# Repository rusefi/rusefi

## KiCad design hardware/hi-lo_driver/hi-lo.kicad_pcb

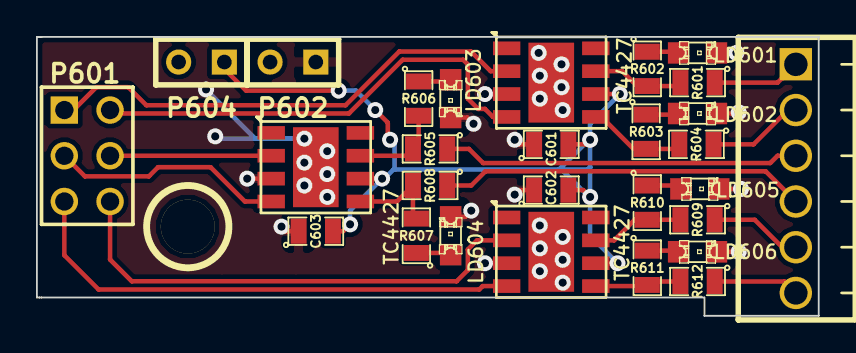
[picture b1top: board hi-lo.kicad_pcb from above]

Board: 2 copper layers, 43.4 x 15.5 mm, 30 parts (1 on the bottom side), 26 nets.

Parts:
C601, C602, C603: 0.1uF; SM0805
G601: LOGO; LOGO_F
LD601, LD602, LD603, LD604, LD605, LD606: LED; LED-0805
M601: CONN_1; 1pin
P601: CONN_3X2; pin_array_3x2
P602, P604: CONN_2; SIL-2
P603: CONN_6; OSTVN06A150
R601, R604, R605, R608, R609, R612: 100; SM0805
R602, R603, R606, R607, R610, R611: 2700; SM0805
U601, U602, U603: TC4427; SOIC8-DFN

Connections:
/HL1: P603.1, R601.1
/HL2: P603.2, R604.1
/HL3: P603.3, R605.1
/HL4: P603.4, R608.1
/HL5: P603.5, R609.1
/HL6: P603.6, R612.1
/H_IN1: P601.2, U601.4
/H_IN2: P601.4, U602.2
/H_IN3: P601.1, U601.2
/H_IN4: P601.3, U602.4
/H_IN5: P601.5, U603.4
/H_IN6: P601.6, U603.2
/VP: C601.2, C602.2, C603.2, P604.1, U601.6, U602.6, U603.6
GND: C601.1, C602.1, C603.1, LD601.2, LD602.2, LD603.2, LD604.2, LD605.2, LD606.2, P602.1, U601.3, U601.9, U602.3, U602.9, U603.3, U603.9
unnamed: LD604.1, R607.1
unnamed: LD602.1, R603.1
unnamed: LD605.1, R610.1
unnamed: LD603.1, R606.1
unnamed: LD601.1, R602.1
unnamed: R609.2, R610.2, U603.7
unnamed: R603.2, R604.2, U601.5
unnamed: R601.2, R602.2, U601.7
unnamed: R607.2, R608.2, U602.5
unnamed: R605.2, R606.2, U602.7
unnamed: LD606.1, R611.1
unnamed: R611.2, R612.2, U603.5

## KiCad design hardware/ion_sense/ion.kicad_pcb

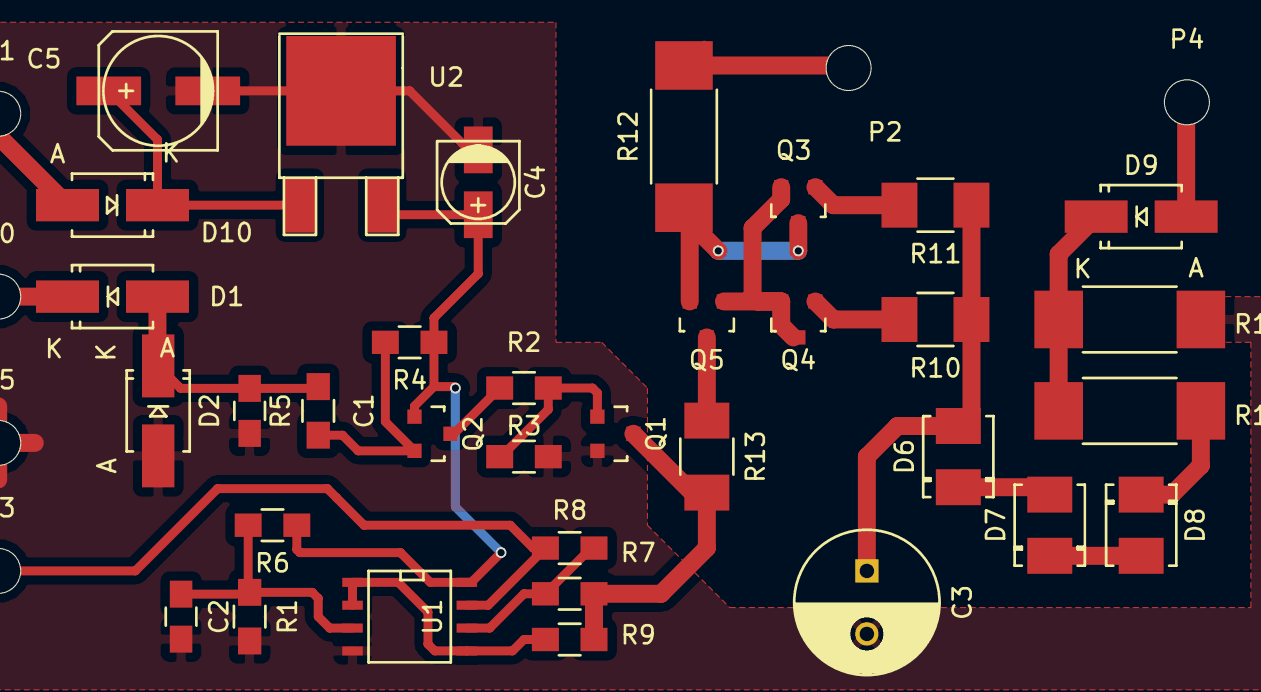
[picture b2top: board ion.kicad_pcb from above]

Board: 2 copper layers, 40 parts (0 on the bottom side), 25 nets.

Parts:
C1: 0.1uF; C_0805_HandSoldering
C2: 1uF; C_0805_HandSoldering
C3: 2.2uF 350V; C_Radial_D8_L11.5_P3.5
C4: 4.7uF 16V; c_elec_4x4.5
C5: 47uF 25V; c_elec_6.3x4.5
D1, D2, D9, D10: US1M; SMA_Handsoldering
D6, D7, D8: 1N4740A; DO-214BA
P0, P1, P2, P3, P4, P5: CONN_01X01; MountingHole_2-5mm
Q1: MMBT3904; SOT-23
Q2, Q3, Q4, Q5: MPSA92; SOT-23
R1, R6, R7, R8: 51k; R_0805_HandSoldering
R2: 2k; R_0805_HandSoldering
R3: 3.9k; R_0805_HandSoldering
R4: 10k; R_0805_HandSoldering
R5: 1k; R_0805_HandSoldering
R9: 4.7k; R_0805_HandSoldering
R10, R11: 560; R_1210_HandSoldering
R12: 180k; R_2512_HandSoldering
R13: 68k; R_1210_HandSoldering
R14: 33k; R_2512_HandSoldering
R15: 1M; R_2512_HandSoldering
U1: LM2904; SOIC-8-N
U2: MC78M05CDT; TO-252-2Lead

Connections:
Earth: C1.2, C2.2, C3.2, C4.2, C5.2, D2.2, P5.1, Q1.2, R1.2, R2.2, R15.1, U1.4, U2.2
unnamed: C1.1, D1.2, D2.1, R5.2
unnamed: C2.1, R1.1, R6.2, U1.3
unnamed: C3.1, D6.2, R10.1, R11.1
unnamed: C4.1, Q2.1, R4.1, R6.1, U1.8, U2.3
unnamed: C5.1, D10.1, U2.1
unnamed: D1.1, P0.1
unnamed: D6.1, D7.2
unnamed: D7.1, D8.2
unnamed: D8.1, R14.2
unnamed: D9.1, R14.1, R15.2
unnamed: D9.2, P4.1
unnamed: D10.2, P1.1
unnamed: P3.1, R8.1, U1.7
unnamed: Q1.1, R2.1, R3.1
unnamed: Q1.3, R7.1, R9.1, R13.2
unnamed: Q2.2, R4.2, R5.1
unnamed: Q2.3, R3.2
unnamed: Q3.1, R11.2
unnamed: Q3.2, Q4.2, Q4.3, Q5.1
unnamed: Q3.3, Q5.2, R12.1
unnamed: Q4.1, R10.2
unnamed: Q5.3, R13.1
unnamed: R7.2, R8.2, U1.6
unnamed: R9.2, U1.1, U1.2, U1.5

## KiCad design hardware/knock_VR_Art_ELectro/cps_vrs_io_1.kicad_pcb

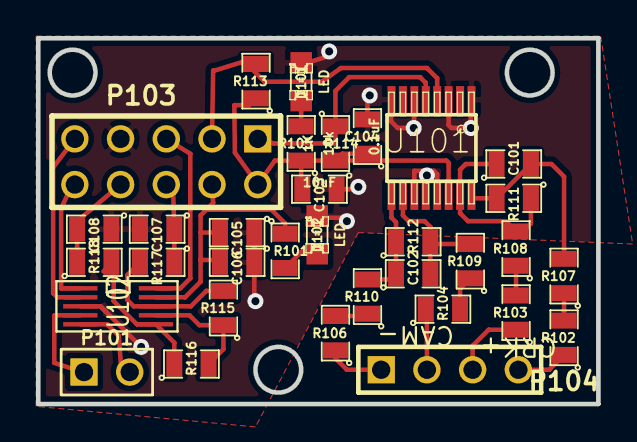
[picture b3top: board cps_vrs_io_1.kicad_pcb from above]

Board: 2 copper layers, 31.1 x 20.3 mm, 34 parts (1 on the bottom side), 29 nets.

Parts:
C101, C102, C108: 1000pF; SM0805
C103: 10uF; SM0805
C104, C106, C107: 0.1uF; SM0805
C105: 1uF; SM0805
D101, D102: LED; LED-0805_A
G101: LOGO; LOGO_F
P101: CONN_2; PIN_ARRAY_2_A
P103: CONN_5X2; PIN_ARRAY_5x2
P104: CONN_4; PIN_ARRAY_4x1
R101, R105: 1K; SM0805
R102, R103, R104, R106, R107, R108, R109, R110, R111, R112: 5k; SM0805
R113, R114: 10k; SM0805
R115, R116: 10K; SM0805
R117, R118: 20K; SM0805
U101: MAX9926/9927; maxim-10-QSOP16
U102: MAX9939; uMAX-uSOP_10

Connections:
/5V: C103.2, C104.1, P103.2, R105.1, R113.1, R114.2, U101.14
/5v stab: C105.2, C106.2, P103.4, R101.1, U102.9
/CAM: P103.1, R114.1, U101.5
/CAM+: P104.1, R106.1
/CAM-: P104.2, R104.1
/CRANK: P103.3, R113.2, U101.4
/CRK2+: P104.4, R102.1
/CRK2-: P104.3, R103.1
/CS-KN1: P103.5, U102.10
/MISO: P103.9, U102.2
/SCK: P103.10, U102.1
/knock1+: C107.1, P103.6, R117.1
/knock1-: C108.2, P103.8, R118.1
/knock_1+p: P101.2, U102.5
/knock_1-p: P101.1, U102.4
GND: C103.1, C104.2, C105.1, C106.1, C107.2, C108.1, D101.2, D102.2, P103.7, U101.1, U101.3, U101.6, U101.8, U101.11, U101.12, U101.13, U102.3
unnamed: R115.1, R116.2, U102.7
unnamed: R115.2, R117.2, U102.8
unnamed: R116.1, R118.2, U102.6
unnamed: D102.1, R101.2
unnamed: D101.1, R105.2
unnamed: R102.2, R107.1
unnamed: R104.2, R109.1
unnamed: R106.2, R110.1
unnamed: R103.2, R108.1
unnamed: C101.1, R108.2, R111.1, U101.15
unnamed: C101.2, R107.2, R111.2, U101.16
unnamed: C102.1, R110.2, R112.1, U101.9
unnamed: C102.2, R109.2, R112.2, U101.10

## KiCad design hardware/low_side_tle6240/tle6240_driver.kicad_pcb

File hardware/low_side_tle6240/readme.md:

TLE6240GP module - integrated low side switch

https://youtu.be/H8Tr4kTaYAI

https://rusefi.com/forum/viewtopic.php?f=4&t=398

All 16 channels can be controlled via the serial interface (SPI). In addition to the serial control it is possible to
control channel 1 to 4 and 9 to 12 direct in parallel with a separate input pin.

https://github.com/rusefi/rusefi_documentation/blob/master/oem_docs/Infineon/Infineon-TLE6240GP-DS-v03_03-en.pdf

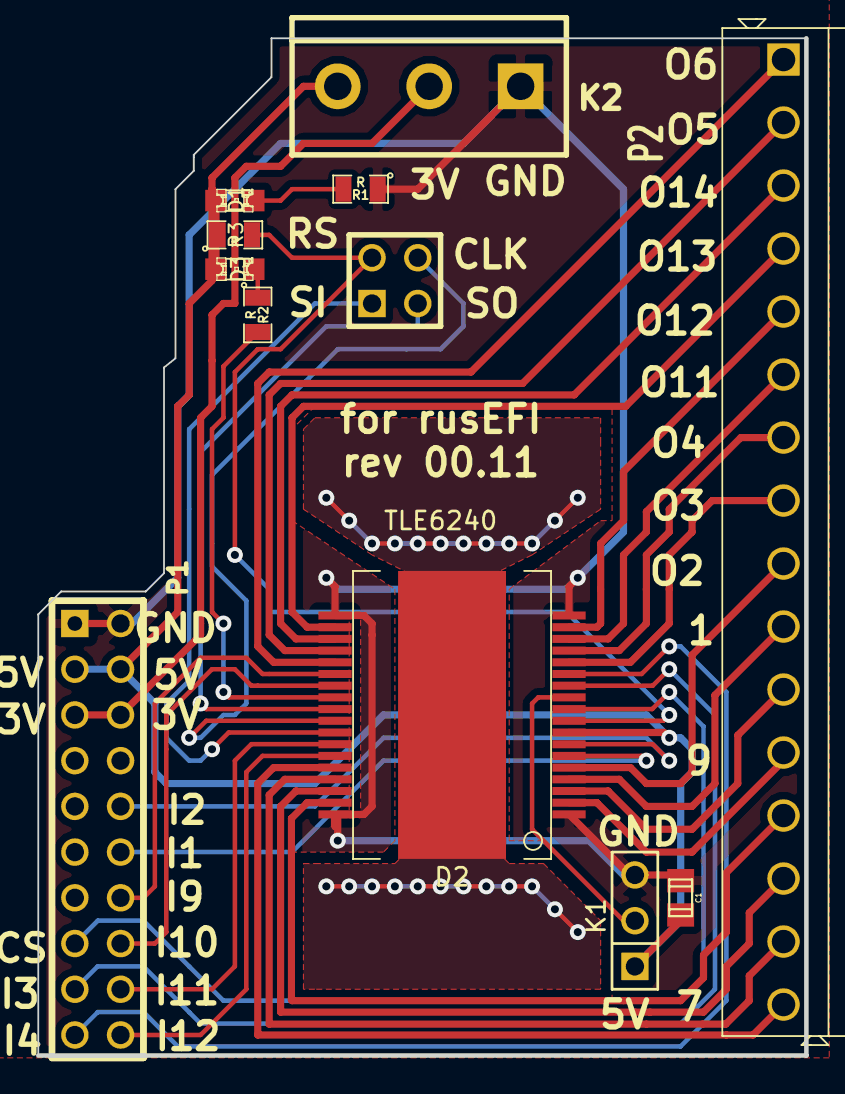
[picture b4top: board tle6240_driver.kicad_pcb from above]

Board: 2 copper layers, 42.7 x 56.5 mm, 12 parts (0 on the bottom side), 36 nets.

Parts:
C1: C; c_0805
D1, D3: LED; LED-0805
D2: TLE6240; PG-DSO-36
K1: JUMPER3; PIN_ARRAY_3X1
K2: CONN_3; bornier3
P1: CONN_10X2; PIN_ARRAY_10X2
P2: CONN_16; SIL-16_3.5MM
P3: CONN_2X2; PIN_ARRAY_2X2
R1, R2, R3: R; SM0805

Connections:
+5V: C1.1, D1.1, D2.8, D3.1, K1.1, K2.3, P1.3, P1.4, R3.1
/+3.3V: K2.2, P1.5, P1.6
/CS: D2.10, P1.15
/Fault: D2.26, R2.2
/IN1: D2.6, P1.12
/IN2: D2.7, P1.10
/IN3: D2.12, P1.17
/IN4: D2.13, P1.19
/IN9: D2.24, P1.14
/IN10: D2.25, P1.16
/IN11: D2.30, P1.18
/IN12: D2.31, P1.20
/OUT1: D2.4, P2.10
/OUT2: D2.5, P2.9
/OUT3: D2.14, P2.8
/OUT4: D2.15, P2.7
/OUT5: D2.22, P2.2
/OUT6: D2.23, P2.1
/OUT7: D2.32, P2.16
/OUT8: D2.33, P2.15
/OUT9: D2.2, P2.12
/OUT10: D2.3, P2.11
/OUT11: D2.16, P2.6
/OUT12: D2.17, P2.5
/OUT13: D2.20, P2.4
/OUT14: D2.21, P2.3
/OUT15: D2.34, P2.14
/OUT16: D2.35, P2.13
/PRG: D2.11, K1.2
/Reset: D2.9, P3.2, R3.2
/SCLK: D2.28, P3.4
/SI: D2.29, P3.1
/SO: D2.27, P3.3
GND: C1.2, D2.1, D2.18, D2.19, D2.36, K1.3, K2.1, P1.1, P1.2, R1.1
unnamed: D3.2, R2.1
unnamed: D1.2, R1.2

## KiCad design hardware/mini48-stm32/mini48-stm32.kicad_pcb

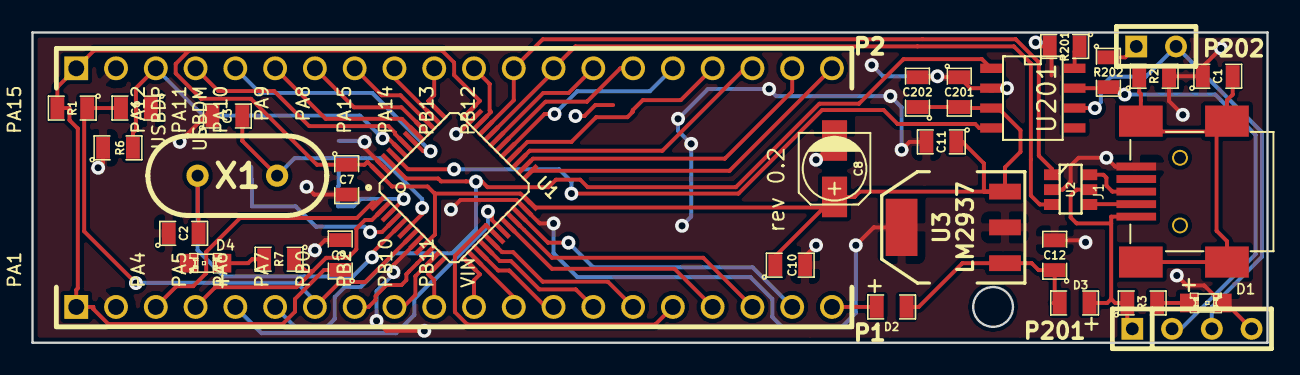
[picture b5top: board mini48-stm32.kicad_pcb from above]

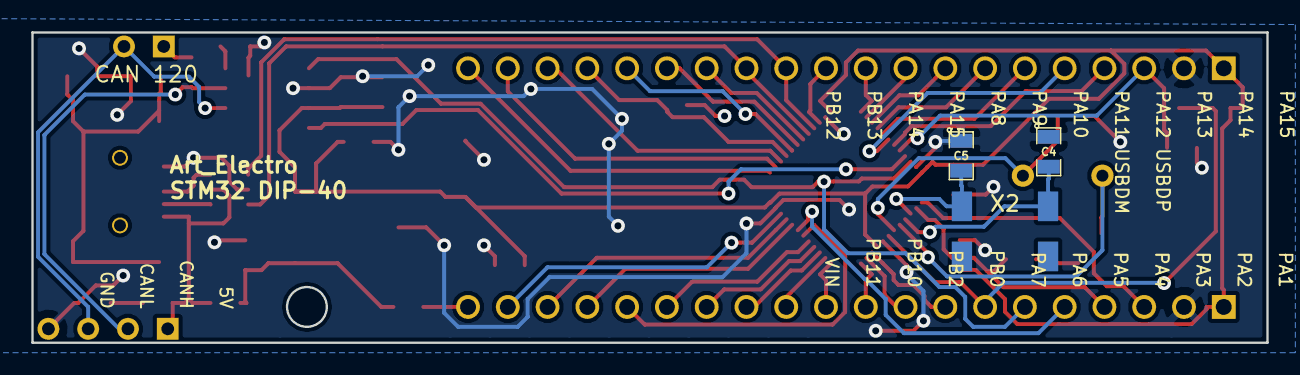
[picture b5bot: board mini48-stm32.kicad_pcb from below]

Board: 2 copper layers, 78.9 x 19.8 mm, 36 parts (3 on the bottom side), 54 nets.

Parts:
C1: 4700pF; SM0805
C2, C3, C4, C5: 18pF; SM0805
C6: 100nF; SM0805
C7, C10, C11: 1uF; SM0805
C8: 47uF; CP_elec_4x5.3
C9, C201: 0.1uF; SM0805
C12: 10uF; SM0805
C202: 4.7uF; SM0805
D1: GREEN; LED-0805_A
D2, D3: DIODESCH; SM0805-diode
D4: BLUE; LED-0805_A
J1: MINI-USB; MINI-USB-5P-3400020P1
P1, P2: CONN_20; PIN_ARRAY_20X1
P201: CONN_4; SIL-4
P202: JUMPER; JUMPER-2
R1, R3, R7: 1k; SM0805
R2: 1M; SM0805
R6, R201: 10k; SM0805
R202: 120; SM0805
U1: STM32F103C8; lqfp48
U2: NUF2101MT1G; SOT-457
U3: LM2937; SOT223
U201: SN65HVD230; SO8E
X1: 8MHz; HC-49V
X2: 32768KHz; MC-306

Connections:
/BOOT0: P2.3, R6.2, U1.44
/CAN BUS/3.3V: C7.1, C8.1, C9.1, C10.1, C11.1, C201.2, C202.1, P1.1, P2.1, R1.2, U1.9, U1.24, U1.36, U1.48, U3.3, U201.3
/CAN BUS/5V: D3.1, J1.1, P201.1, R3.1, U2.5
/CAN BUS/CANH: P201.2, R202.2, U201.7
/CAN BUS/CANL: P201.3, P202.2, U201.6
/CAN BUS/CAN_RX: U1.45, U201.4
/CAN BUS/CAN_TX: P1.6, U1.46, U201.1
/D+: J1.3, U2.6
/D-: J1.2, U2.4
/PA0: P1.8, U1.10
/PA1: P1.9, U1.11
/PA2: P1.10, U1.12
/PA3: P1.11, U1.13
/PA4: P1.12, U1.14
/PA5: P1.13, U1.15
/PA6: P1.14, U1.16
/PA7: P1.15, U1.17
/PA8: P2.16, U1.29
/PA9: P2.15, U1.30
/PA10: P2.14, U1.31
/PA11_USBDM: P2.13, U1.32, U2.3
/PA12_USBDP: P2.12, U1.33, U2.1
/PA13: P2.11, U1.34
/PA14: P2.10, U1.37
/PA15: P2.9, U1.38
/PB0: P1.16, U1.18
/PB1: P1.5, U1.19
/PB2: P1.17, U1.20
/PB3: P2.8, U1.39
/PB4: P2.7, U1.40
/PB5: P2.6, U1.41
/PB6: P2.5, U1.42
/PB7: P2.4, U1.43
/PB10: P1.18, U1.21
/PB11: P1.19, U1.22
/PB12: P2.20, U1.25
/PB13: P2.19, U1.26
/PB14: P2.18, U1.27
/PB15: P2.17, U1.28
/PC13: P1.4, R7.1, U1.2
/PC14_OSC32_IN: C5.2, U1.3, X2.2
/PC15_OSC32_OUT: C4.2, U1.4, X2.1
/PD0: C2.2, U1.5, X1.1
/PD1: C3.2, U1.6, X1.2
/Reset: C6.2, P1.7, R1.1, U1.7
/VBAT: P1.3, U1.1
/VIN: D2.1, P1.20
GND: C1.1, C2.1, C3.1, C4.1, C5.1, C6.1, C7.2, C8.2, C9.2, C10.2, C11.2, C12.2, C201.1, C202.2, D1.2, D4.2, J1.5, P1.2, P2.2, P201.4, R2.2, R6.1, R201.2, U1.8, U1.23, U1.35, U1.47, U2.2, U3.2, U3.4, U201.2
unnamed: C12.1, D2.2, D3.2, U3.1
unnamed: D4.1, R7.2
unnamed: D1.1, R3.2
unnamed: C1.2, J1.6, R2.1
unnamed: P202.1, R202.1
unnamed: R201.1, U201.8

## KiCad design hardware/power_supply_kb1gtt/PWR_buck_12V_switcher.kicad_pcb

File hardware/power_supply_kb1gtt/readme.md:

Older version of the power supply with SMD inductors

For current version with three inductors see [frankenso-PWR-Supply](../frankenso-PWR-Supply)

https://rusefi.com/forum/viewtopic.php?f=4&t=394

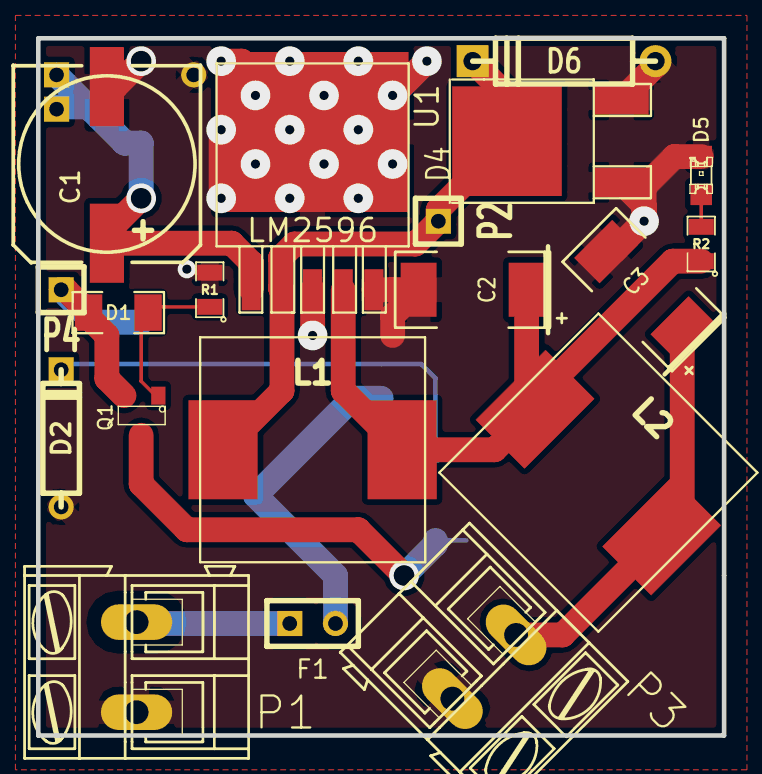
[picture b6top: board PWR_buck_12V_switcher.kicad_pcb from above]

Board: 2 copper layers, 38.1 x 38.7 mm, 24 parts (0 on the bottom side), 12 nets.

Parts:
C1: 330uF 35V; SMDSVP10
C2, C3: 220uF 16V; SM2512
D1: 7.5V; SM1206
D2: 14V; D3
D3: 24V; D3
D4: SCHDPAK; DPAK2
D5: LED-grn; LED-0805
D6: DIODESCH; D4
F1: 5A; SIL-2
L1, L2, L3: 38uH; SM100uH
P1, P3: CONN_2; AK300-2
P2, P4, P5: CONN_1; SIL-1
Q1: 20V; SOT23
Q2: 200V; m-pad-2.1-TO-263AB
R1: 39k; SM0805
R2: 1k; SM0805
R3: 100k; SM0805
U1: LM2596; DPAK5

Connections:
/5V-REG: C3.1, L2.2, P3.1
/FB: C2.1, L1.2, L2.1, R2.1, U1.4
/OUT: D4.2, D6.2, L1.1, P2.1, U1.2
/VBAT: C1.1, D3.2, L3.2, P5.1, U1.1
/Vf: F1.2, Q2.2, R3.1
/Vin: F1.1, P1.2
/Vs1: D2.2, Q2.1, R3.2
/Vs2: Q1.3, Q2.3
GND: C1.2, C2.2, C3.2, D2.1, D3.1, D4.1, D4.3, D5.2, D6.1, P1.1, P3.2, R1.2, U1.3, U1.5
unnamed: D1.1, Q1.1, R1.1
unnamed: D1.2, L3.1, P4.1, Q1.2
unnamed: D5.1, R2.2

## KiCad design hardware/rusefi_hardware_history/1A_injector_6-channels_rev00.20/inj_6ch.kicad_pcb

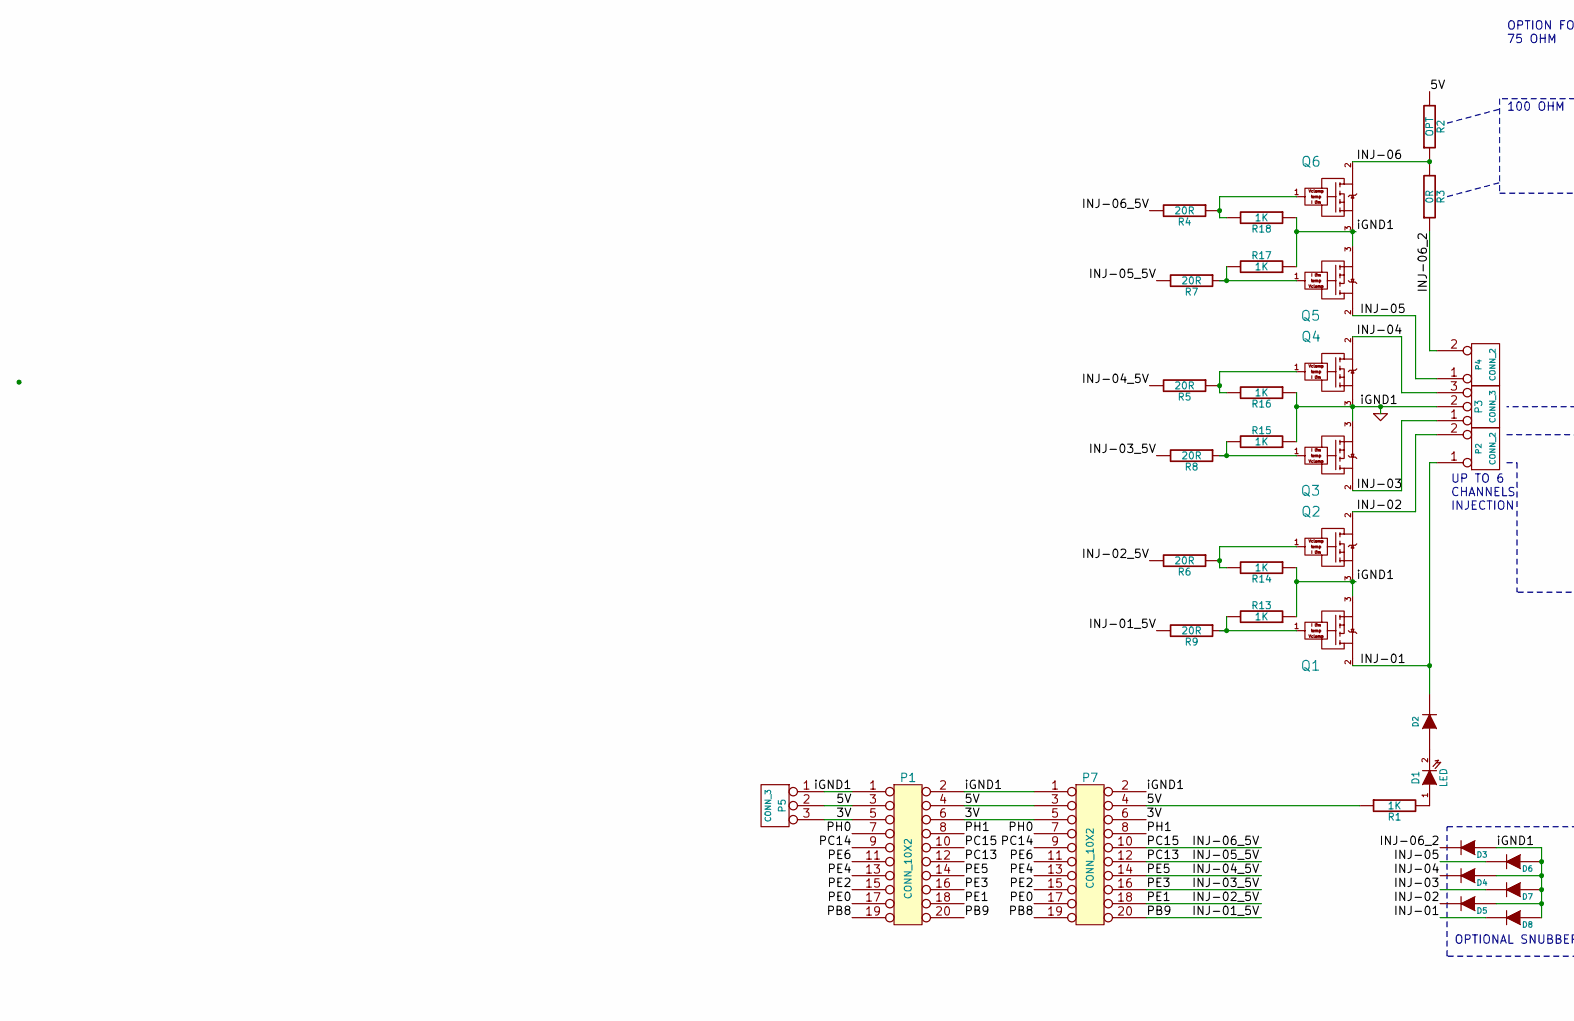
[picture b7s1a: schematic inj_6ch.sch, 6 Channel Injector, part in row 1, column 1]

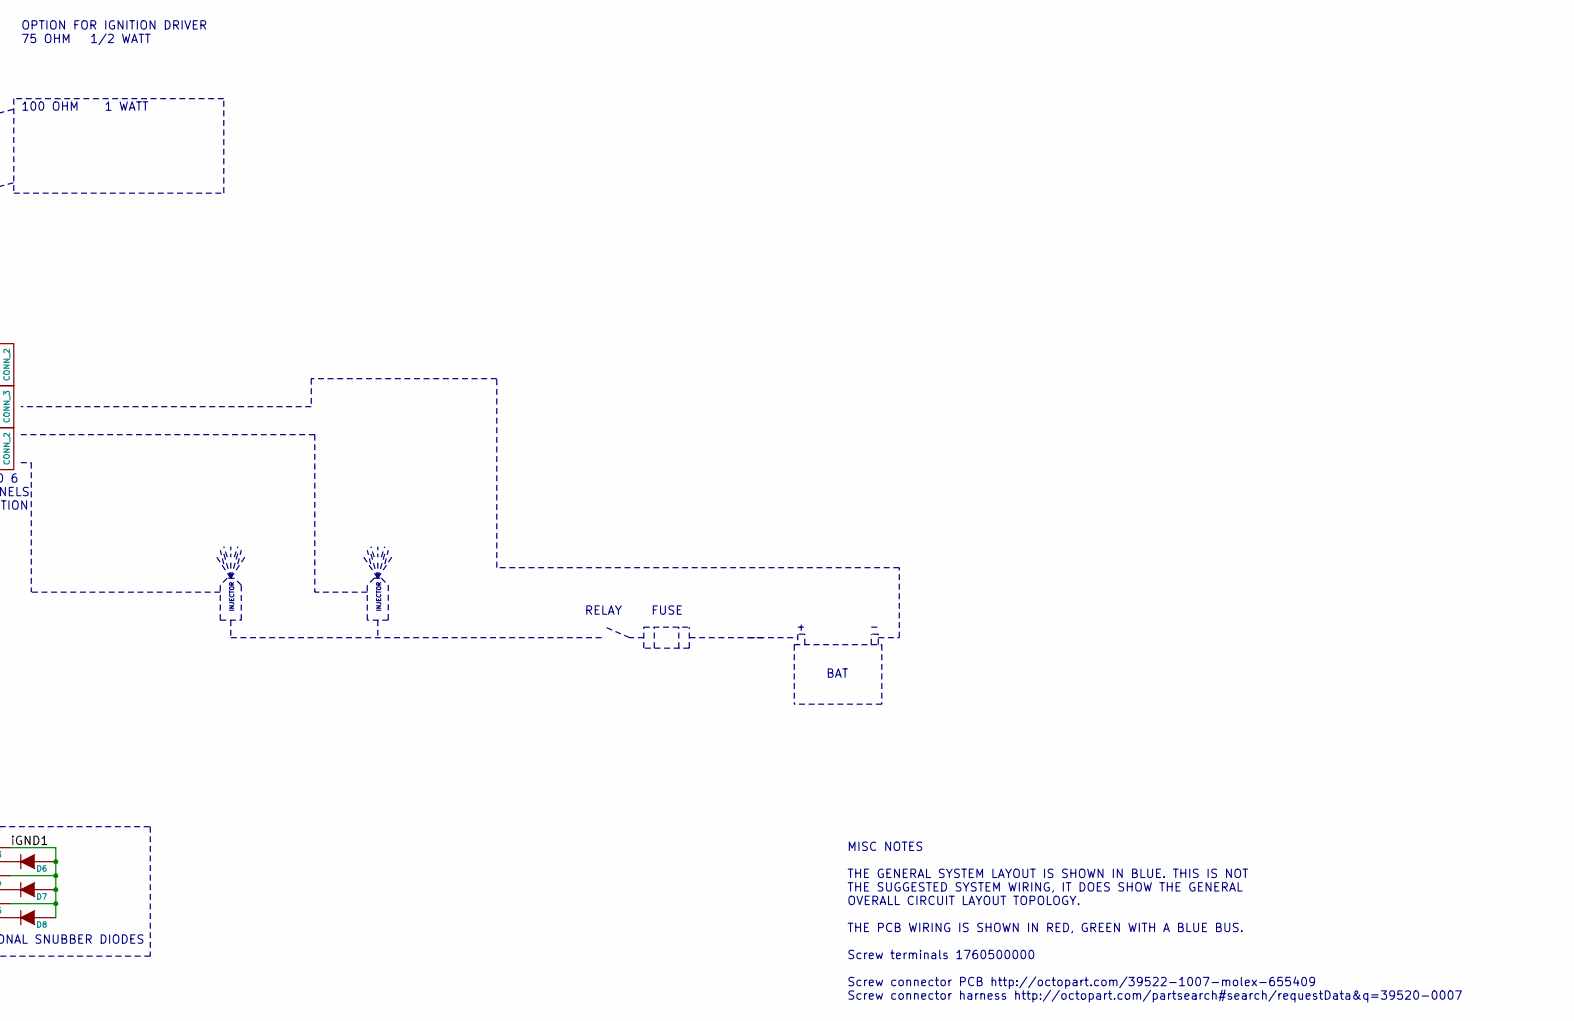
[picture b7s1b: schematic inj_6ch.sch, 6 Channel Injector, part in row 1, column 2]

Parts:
D1: LED; LED-0805
D2: DIODE; SOD-123
D3, D4, D5, D6, D7, D8: DIODE; SIL-2
P1, P7: CONN_10X2; pin_array_10x2
P2, P4: CONN_2; bornier2
P3, P5: CONN_3; bornier3; mfg# 1760500000
Q1, Q2, Q3, Q4, Q5, Q6: OVP_DRIVER; SO8E_ST
R1, R13, R14, R15, R16, R17, R18: 1K; SM0805
R2: OPT; SIL-2
R3: 0R; SIL-2
R4, R5, R6, R7, R8, R9: 20R; SM0805

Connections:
/3V: P1.5, P1.6, P5.3, P7.5, P7.6
/5V: P1.3, P1.4, P5.2 (PM), P7.3, P7.4, R1.1, R2.2
/INJ-01: D2.2 (K), D8.2 (K), P2.1, Q1.2 (C)
/INJ-01_5V: P1.20, P7.20, R9.2
/INJ-02: D5.2 (K), P2.2 (PM), Q2.2 (C)
/INJ-02_5V: P1.18, P7.18, R6.2
/INJ-03: D7.2 (K), P3.1, Q3.2 (C)
/INJ-03_5V: P1.16, P7.16, R8.2
/INJ-04: D4.2 (K), P3.3, Q4.2 (C)
/INJ-04_5V: P1.14, P7.14, R5.2
/INJ-05: D6.2 (K), P4.1, Q5.2 (C)
/INJ-05_5V: P1.12, P7.12, R7.2
/INJ-06: Q6.2 (C), R2.1, R3.2
/INJ-06_2: D3.2 (K), P4.2 (PM), R3.1
/INJ-06_5V: P1.10, P7.10, R4.2
/PB8: P1.19, P7.19
/PC14: P1.9, P7.9
/PE0: P1.17, P7.17
/PE2: P1.15, P7.15
/PE4: P1.13, P7.13
/PE6: P1.11, P7.11
/PH0: P1.7, P7.7
/PH1: P1.8, P7.8
GND: D3.1 (A), D4.1 (A), D5.1 (A), D6.1 (A), D7.1 (A), D8.1 (A), P1.1, P1.2, P3.2 (PM), P5.1, P7.1, P7.2, Q1.3 (E), Q2.3 (E), Q3.3 (E), Q4.3 (E), Q5.3 (E), Q6.3 (E), R13.1, R14.1, R15.1, R16.1, R17.1, R18.1
unnamed: D1.1 (A), R1.2
unnamed: D1.2 (K), D2.1 (A)
unnamed: Q6.1 (G), R4.1, R18.2
unnamed: Q4.1 (G), R5.1, R16.2
unnamed: Q3.1 (G), R8.1, R15.2
unnamed: Q2.1 (G), R6.1, R14.2
unnamed: Q1.1 (G), R9.1, R13.2
unnamed: Q5.1 (G), R7.1, R17.2

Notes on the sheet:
INJECTOR
RELAY
UP TO 6 CHANNELS INJECTION
MISC NOTES THE GENERAL SYSTEM LAYOUT IS SHOWN IN BLUE. THIS IS NOT THE SUGGESTED SYSTEM WIRING, IT DOES SHOW THE GENERAL OVERALL CIRCUIT LAYOUT TOPOLOGY. THE PCB WIRING IS SHOWN IN RED, GREEN WITH A BLUE BUS. Screw terminals 1760500000 Screw connector PCB http://octopart.com/39522-1007-molex-655409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
BAT
FUSE
OPTIONAL SNUBBER DIODES
OPTION FOR IGNITION DRIVER 75 OHM 1/2 WATT 100 OHM 1 WATT

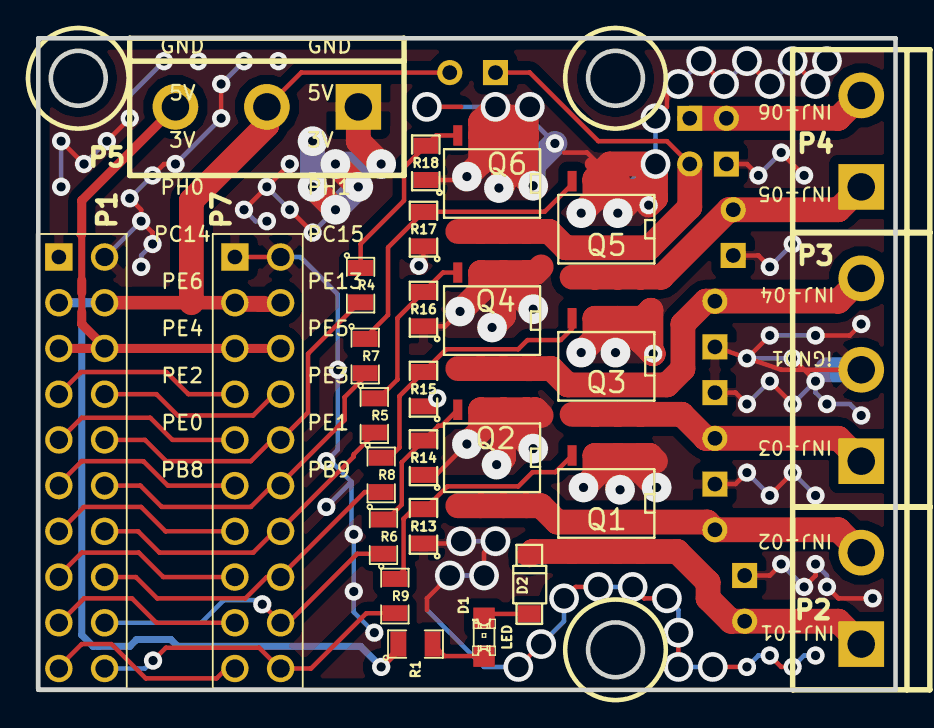
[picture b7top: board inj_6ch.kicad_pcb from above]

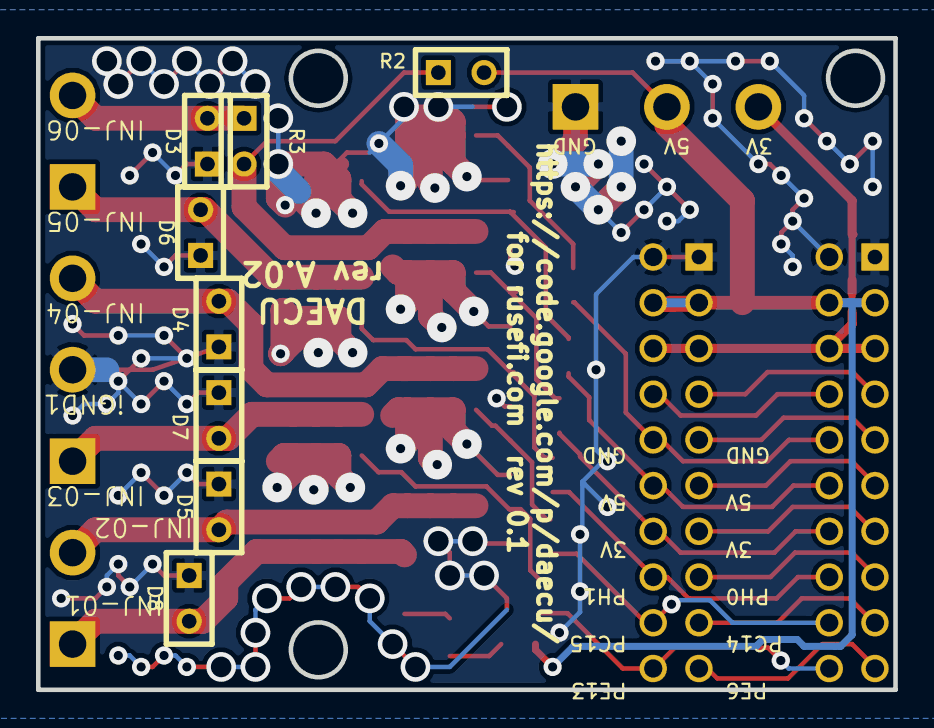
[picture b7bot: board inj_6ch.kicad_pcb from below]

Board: 2 copper layers, 47.6 x 36.2 mm, 35 parts (8 on the bottom side), 32 nets.
